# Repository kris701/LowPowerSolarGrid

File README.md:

# Low Power Solar Grid
A project to make a low power solar setup with a hybrid switcher
The general idea is that most small scale solar chargers and controllers you can buy, takes a lot of base load power.
Say, if you have 300W of solar capacity, its a bit wasteful for the charge controller to be constantly eating 5-10W all day long.

So the general idea is to make a very low power setup that can work with little to no base load.

For this, there are 2 main components, the Low Power Solar Charger and the Low Power Power Switch.
The Charger part adds an extra controller before the charge controller step, which has a Arduino in a low power setup that switches power on and off the 
controller depending on how much light comes in from a light sensor outside. The switches are bistatic relay, so they effectively dont use any base load.
The controller itself uses less than a watt (i cant measure any lower).

The Power Switch part is to have a continuous supply of 12V power to the systems that use it.
It measures the voltage on the battery, and when the voltage is sufficiently high, draws power from the battery. If its too low, it instead draws power
from a 230V to 12V charger.

Everything in the 12V range is connected by Anderson connectors to make a unified connector for everything.

Keep in mind that this is a low power setup, so dont expect to draw more than 200-300W from this setup.

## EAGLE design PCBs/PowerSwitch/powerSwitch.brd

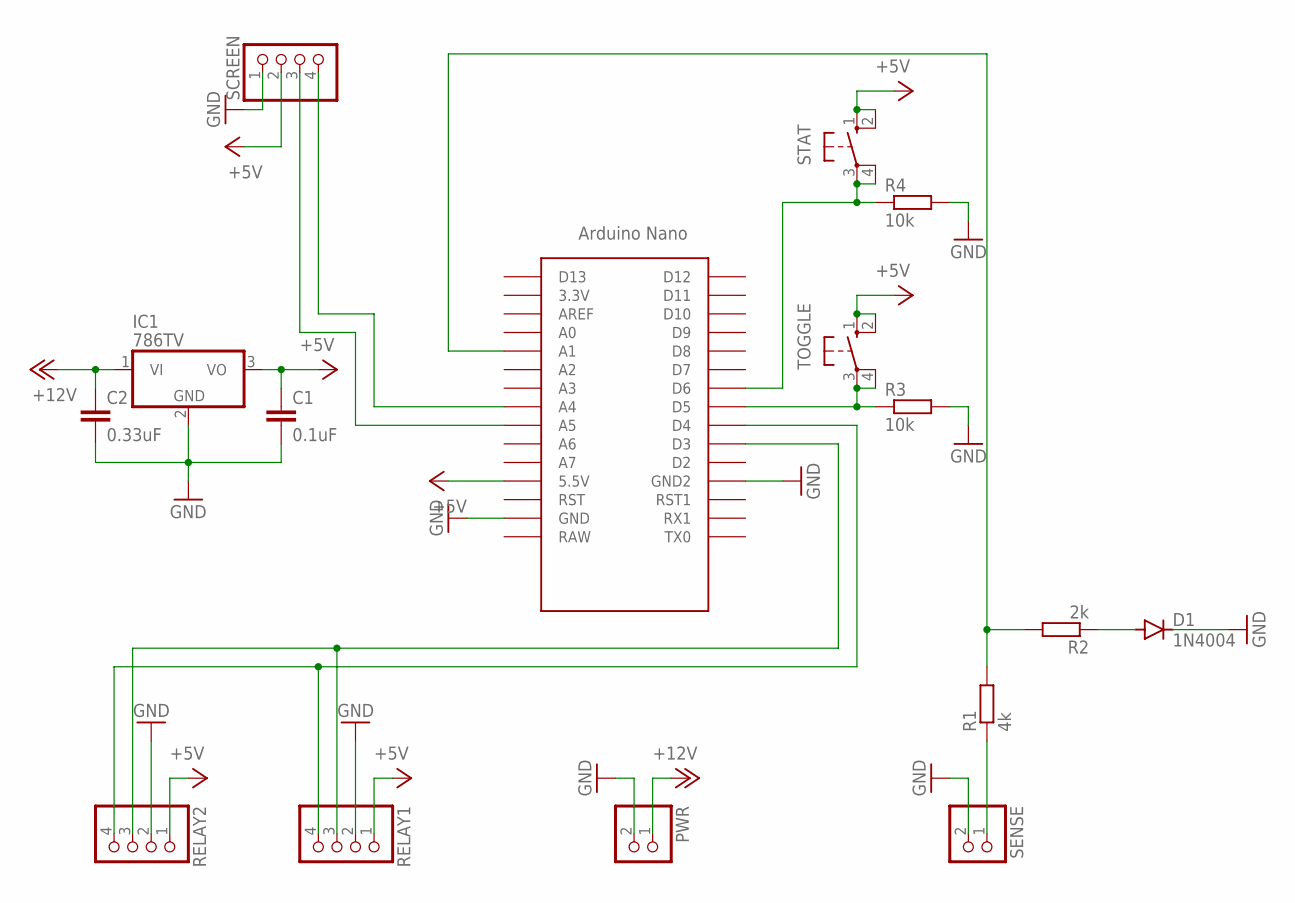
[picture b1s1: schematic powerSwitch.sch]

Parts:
C1: 0.1uF; C5B2.5
C2: 0.33uF; C5B2.5
D1: 1N4004; DO41-10
IC1: 786TV; TO220V
NANO: NANO
PWR: PINHD-1X2; 1X02
R1: 4k; 0204/7
R2: 2k; 0204/7
R3, R4: 10k; 0204/7
RELAY1, RELAY2: PINHD-1X4; 1X04
SCREEN: PINHD-1X4; 1X04
SENSE: PINHD-1X2; 1X02
STAT: 10-XX; B3F-10XX
TOGGLE: 10-XX; B3F-10XX

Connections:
+5V: C1.1, IC1.3 (VO), NANO.5V (5.5V), RELAY1.1, RELAY2.1, SCREEN.2, STAT.1 (S), STAT.2 (S1), TOGGLE.1 (S), TOGGLE.2 (S1)
+12V: C2.1, IC1.1 (VI), PWR.1
GND: C1.2, C2.2, D1.C, IC1.2 (GND), NANO.GND, NANO.GND1 (GND2), PWR.2, R3.2, R4.2, RELAY1.2, RELAY2.2, SCREEN.1, SENSE.2
unnamed: NANO.D3, RELAY1.3, RELAY2.3
unnamed: NANO.D4, RELAY1.4, RELAY2.4
unnamed: R1.1, SENSE.1
unnamed: NANO.A1, R1.2, R2.2
unnamed: D1.A, R2.1
unnamed: NANO.D5, R3.1, TOGGLE.3, TOGGLE.4 (P1)
unnamed: NANO.D6, R4.1, STAT.3, STAT.4 (P1)
unnamed: NANO.A5, SCREEN.3
unnamed: NANO.A4, SCREEN.4

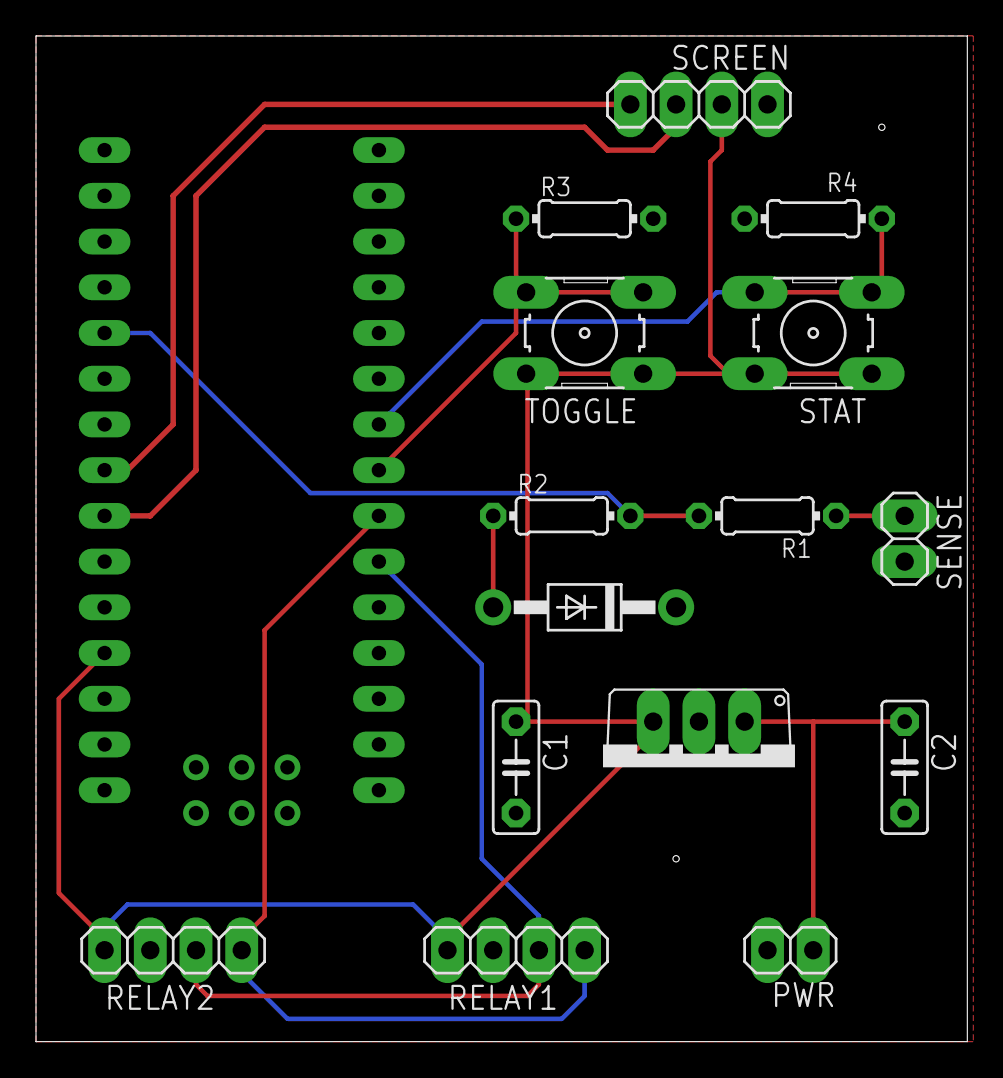
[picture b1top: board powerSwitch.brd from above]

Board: 2 copper layers, 51.7 x 55.9 mm, 16 parts (0 on the bottom side), 12 nets.

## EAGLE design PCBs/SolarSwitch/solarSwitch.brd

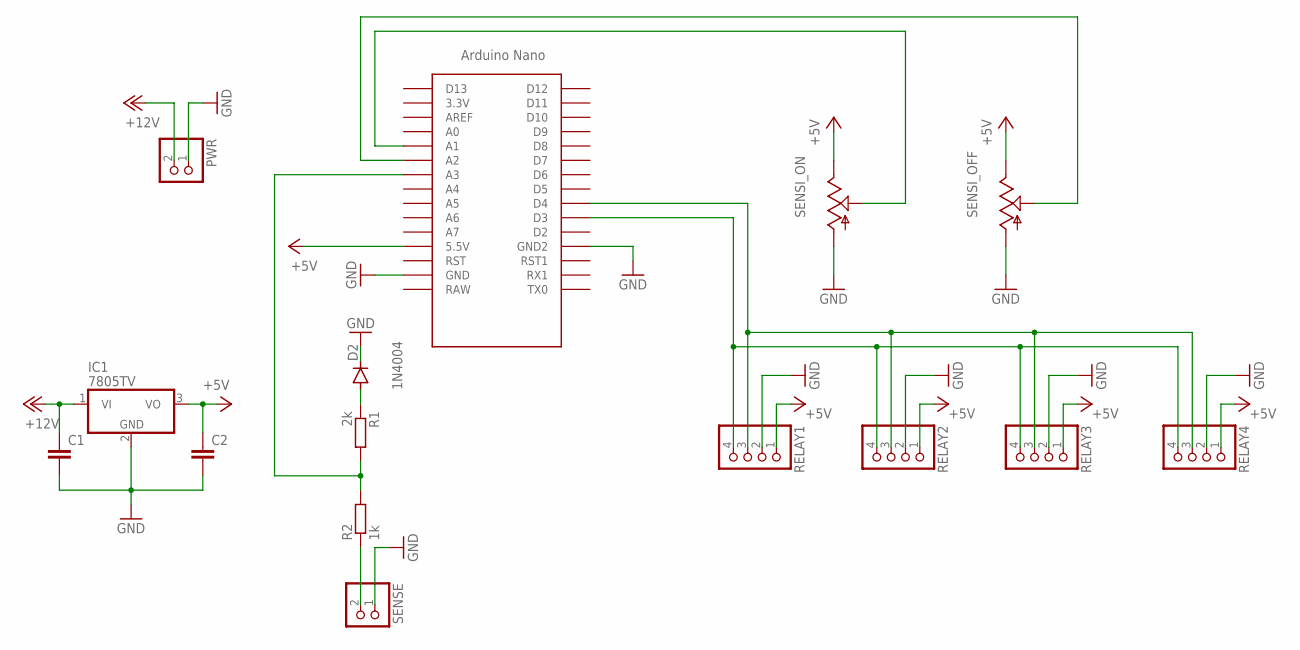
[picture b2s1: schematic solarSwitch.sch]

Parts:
C1, C2: C5/3; C5B3
D2: 1N4004; DO41-10
IC1: 7805TV; TO220V
PWR: PINHD-1X2; 1X02
R1: 2k; 0204/7
R2: 1k; 0204/7
RELAY1, RELAY2, RELAY3, RELAY4: PINHD-1X4; 1X04
SENSE: PINHD-1X2; 1X02
SENSI_OFF: TRIM_US-B25P; B25P
SENSI_ON: TRIM_US-B25P; B25P
U$1: NANO

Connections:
+5V: C2.1, IC1.3 (VO), RELAY1.1, RELAY2.1, RELAY3.1, RELAY4.1, SENSI_OFF.E, SENSI_ON.E, U$1.5V (5.5V)
+12V: C1.1, IC1.1 (VI), PWR.2
GND: C1.2, C2.2, D2.C, IC1.2 (GND), PWR.1, RELAY1.2, RELAY2.2, RELAY3.2, RELAY4.2, SENSE.1, SENSI_OFF.A, SENSI_ON.A, U$1.GND, U$1.GND1 (GND2)
unnamed: SENSI_ON.S, U$1.A1
unnamed: R2.1, SENSE.2
unnamed: D2.A, R1.1
unnamed: SENSI_OFF.S, U$1.A2
unnamed: RELAY1.3, RELAY2.3, RELAY3.3, RELAY4.3, U$1.D4
unnamed: R1.2, R2.2, U$1.A3
unnamed: RELAY1.4, RELAY2.4, RELAY3.4, RELAY4.4, U$1.D3

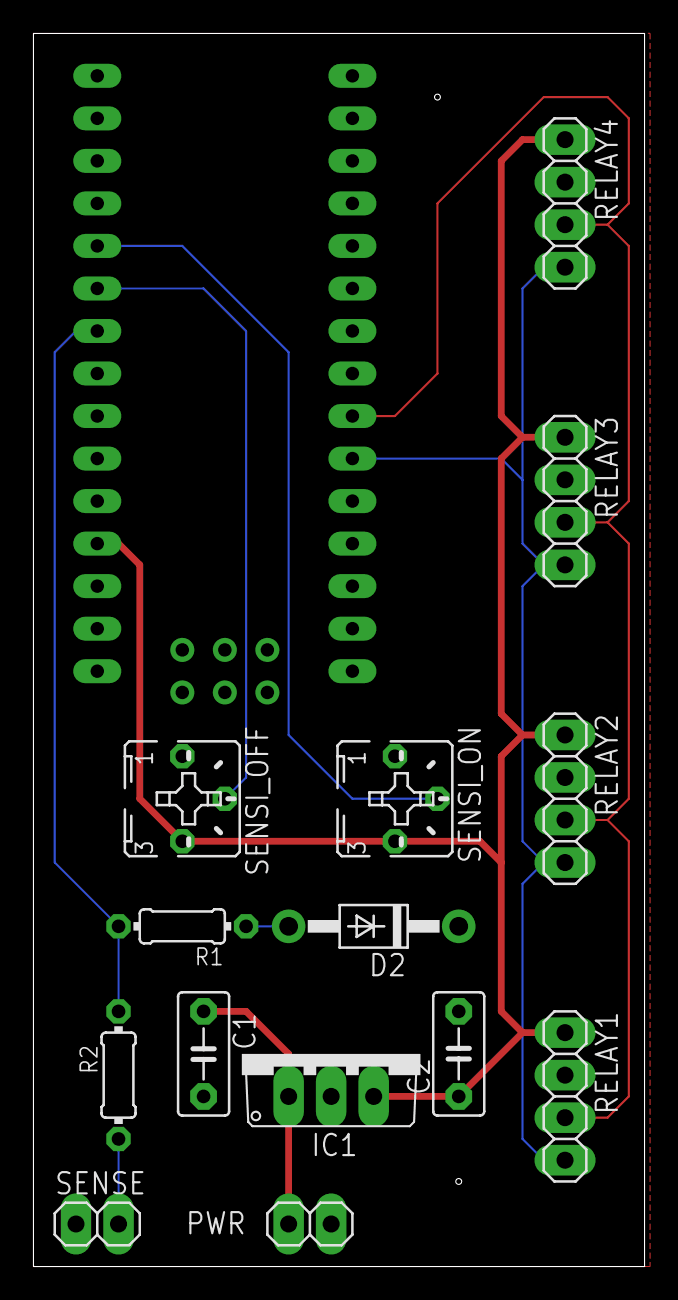
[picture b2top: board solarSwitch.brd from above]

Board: 2 copper layers, 36.5 x 73.7 mm, 15 parts (0 on the bottom side), 10 nets.
